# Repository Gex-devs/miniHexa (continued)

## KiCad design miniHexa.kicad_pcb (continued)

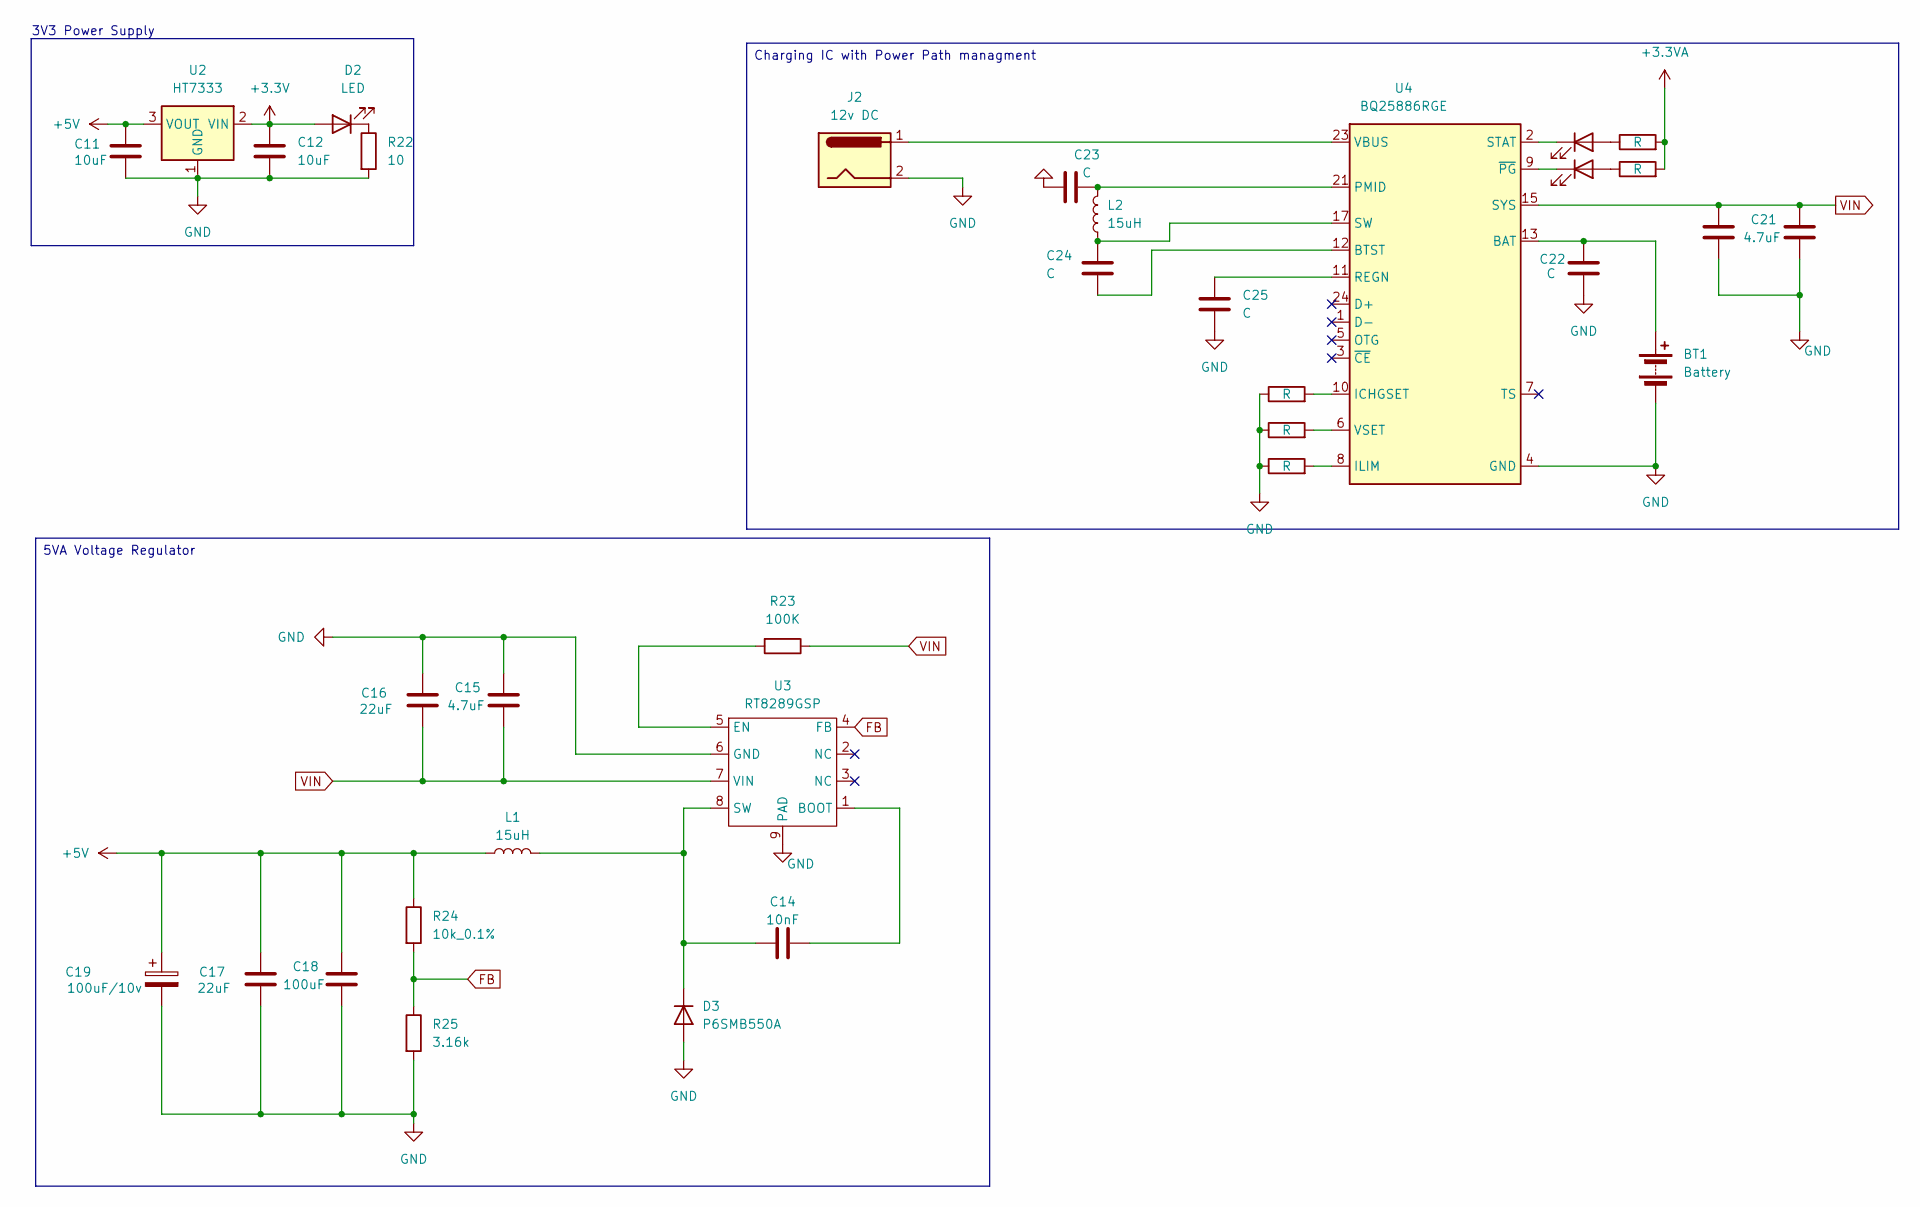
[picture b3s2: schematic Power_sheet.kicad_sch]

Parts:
BT1: Battery
C11, C12: 10uF; C_0805_2012Metric
C14: 10nF; C_0805_2012Metric
C15, C21: 4.7uF; C_0805_2012Metric
C16, C17, C20: 22uF; C_0805_2012Metric
C18: 100uF; C_0805_2012Metric
C19: 100uF/10v; C_0805_2012Metric
C22, C23, C24, C25: C; C_0805_2012Metric
D2, D4, D5: LED; LED_0805_2012Metric
D3: P6SMB550A; D_0805_2012Metric_Pad1.15x1.40mm_HandSolder
J2: 12v DC; BarrelJack_Wuerth_694102107102_1.0x3.9mm
L1, L2: 15uH; L_APV_APH0850
R22: 10; R_0805_2012Metric
R23: 100K; R_0805_2012Metric
R24: 10k_0.1%; R_0805_2012Metric
R25: 3.16k; R_0805_2012Metric
R26, R27, R28, R30, R31: R; R_0805_2012Metric
U2: HT7333; SOT-89-3
U3: RT8289GSP
U4: BQ25886RGE; Texas_RGE0024H_VQFN-24-1EP_4x4mm_P0.5mm_EP2.7x2.7mm

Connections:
+3.3V: C12.1, D2.2 (A), R27.2, R28.2, U2.2 (VIN); also elsewhere on the board
+5V: C11.1, C17.2, C18.2, C19.1, L1.1, R24.1, U2.3 (VOUT); also elsewhere on the board
FB: R24.2, R25.1, U3.4 (FB)
GND: BT1.2 (GND), C11.2, C12.2, C15.2, C16.2, C17.1, C18.1, C19.2, C20.1, C21.1, C22.2, C23.1, C25.2, D3.2 (A), J2.2, R22.2, R25.2, R26.1, R30.1, R31.1, U2.1 (GND), U3.6 (GND), U3.9 (PAD), U4.4 (GND), U4.19 (GND), U4.20 (GND), U4.25 (GND); also elsewhere on the board
unnamed: BT1.1 (+), C22.1, U4.13 (BAT), U4.14 (BAT)
unnamed: C23.2, L2.2, U4.21 (PMID), U4.22 (PMID)
unnamed: C24.1, L2.1, U4.17 (SW), U4.18 (SW)
unnamed: D2.1 (K), R22.1
unnamed: C14.1, D3.1 (K), L1.2, U3.8 (SW)
unnamed: D4.2 (A), R27.1
unnamed: D4.1 (K), U4.2 (STAT)
unnamed: D5.2 (A), R28.1
unnamed: D5.1 (K), U4.9 (~PG)
unnamed: C14.2, U3.1 (BOOT)
unnamed: R23.2, U3.5 (EN)
unnamed: C24.2, U4.12 (BTST)
unnamed: R26.2, U4.10 (ICHGSET)
unnamed: R31.2, U4.8 (ILIM)
unnamed: C25.1, U4.11 (REGN)
unnamed: J2.1, U4.23 (VBUS)
unnamed: R30.2, U4.6 (VSET)
VIN: C15.1, C16.1, C20.2, C21.2, R23.1, U3.7 (VIN), U4.15 (SYS), U4.16 (SYS)

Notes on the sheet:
3V3 Power Supply
Charging IC with Power Path managment
5VA Voltage Regulator

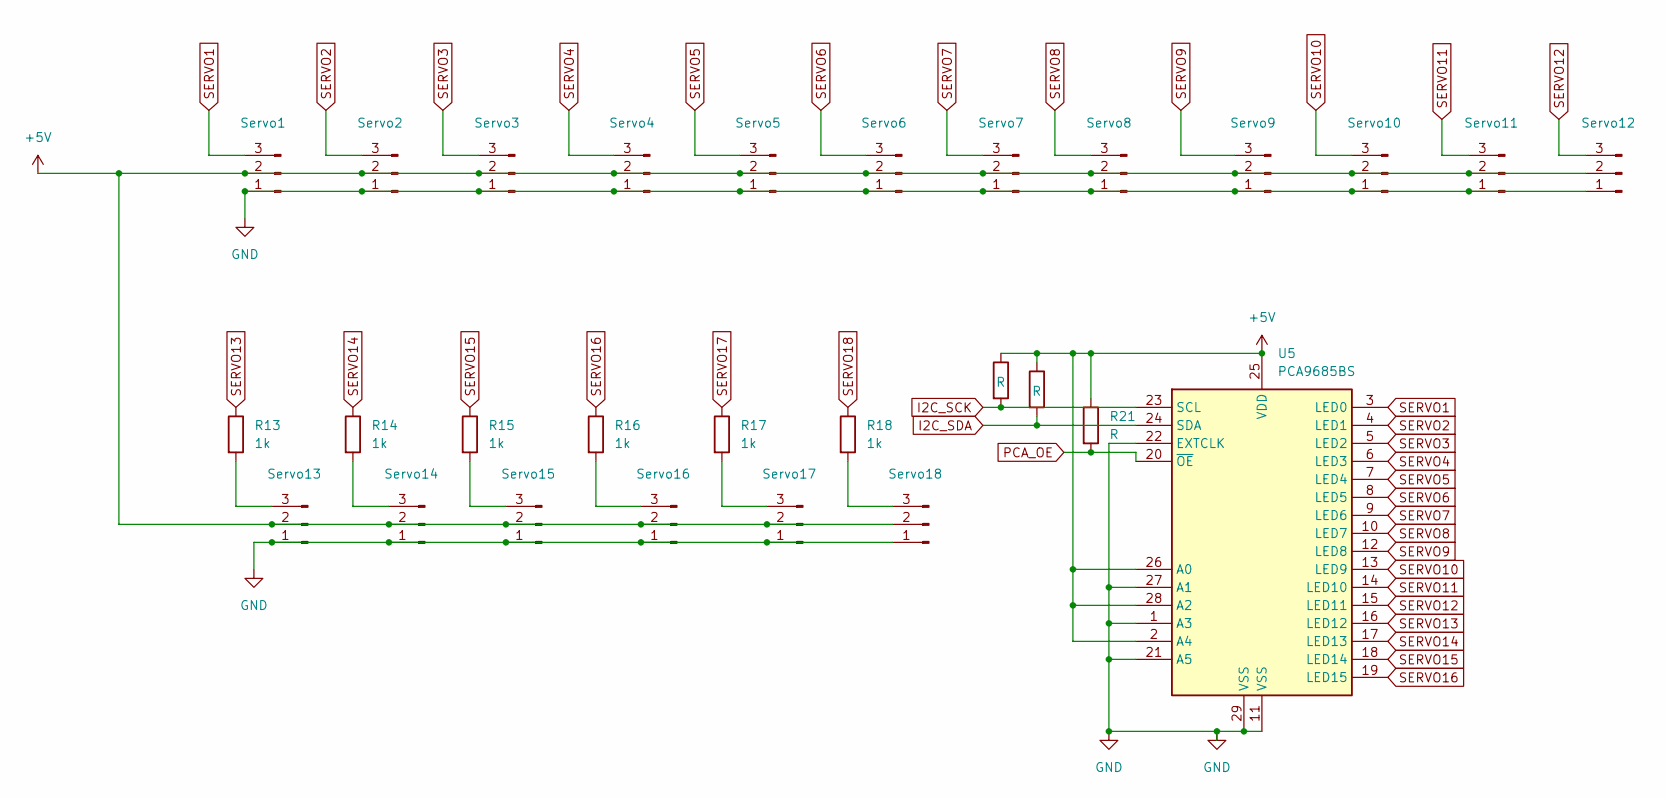
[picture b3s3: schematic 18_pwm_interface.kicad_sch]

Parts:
R13, R14, R15, R16, R17, R18: 1k; R_0805_2012Metric
R19, R20, R21: R; R_0805_2012Metric
Servo1, Servo2, Servo3, Servo4, Servo5, Servo6, Servo7, Servo8, Servo9, Servo10, Servo11, Servo12, Servo13, Servo14, Servo15, Servo16, Servo17, Servo18: Conn_01x03_Pin; JST_XH_B3B-XH-AM_1x03_P2.50mm_Vertical
U5: PCA9685BS; QFN-28-1EP_6x6mm_P0.65mm_EP4.25x4.25mm

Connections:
+5V: R19.1, R20.1, R21.1, Servo1.2, Servo2.2, Servo3.2, Servo4.2, Servo5.2, Servo6.2, Servo7.2, Servo8.2, Servo9.2, Servo10.2, Servo11.2, Servo12.2, Servo13.2, Servo14.2, Servo15.2, Servo16.2, Servo17.2, Servo18.2, U5.2 (A4), U5.25 (VDD), U5.26 (A0), U5.28 (A2); also elsewhere on the board
GND: Servo1.1, Servo2.1, Servo3.1, Servo4.1, Servo5.1, Servo6.1, Servo7.1, Servo8.1, Servo9.1, Servo10.1, Servo11.1, Servo12.1, Servo13.1, Servo14.1, Servo15.1, Servo16.1, Servo17.1, Servo18.1, U5.1 (A3), U5.11 (VSS), U5.21 (A5), U5.22 (EXTCLK), U5.27 (A1), U5.29 (VSS); also elsewhere on the board
I2C_SCK: R19.2, U5.23 (SCL); also elsewhere on the board
I2C_SDA: R20.2, U5.24 (SDA); also elsewhere on the board
unnamed: R13.2, Servo13.3
unnamed: R14.2, Servo14.3
unnamed: R15.2, Servo15.3
unnamed: R16.2, Servo16.3
unnamed: R17.2, Servo17.3
unnamed: R18.2, Servo18.3
PCA_OE: R21.2, U5.20 (~OE)
SERVO1: Servo1.3, U5.3 (LED0)
SERVO2: Servo2.3, U5.4 (LED1)
SERVO3: Servo3.3, U5.5 (LED2)
SERVO4: Servo4.3, U5.6 (LED3)
SERVO5: Servo5.3, U5.7 (LED4)
SERVO6: Servo6.3, U5.8 (LED5)
SERVO7: Servo7.3, U5.9 (LED6)
SERVO8: Servo8.3, U5.10 (LED7)
SERVO9: Servo9.3, U5.12 (LED8)
SERVO10: Servo10.3, U5.13 (LED9)
SERVO11: Servo11.3, U5.14 (LED10)
SERVO12: Servo12.3, U5.15 (LED11)
SERVO13: R13.1, U5.16 (LED12)
SERVO14: R14.1, U5.17 (LED13)
SERVO15: R15.1, U5.18 (LED14)
SERVO16: R16.1, U5.19 (LED15)
SERVO17: R17.1; also elsewhere on the board
SERVO18: R18.1; also elsewhere on the board

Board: 2 copper layers, 78 parts (2 on the bottom side), 58 nets, no tracks yet.

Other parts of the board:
MK-L1: INMP441-L; MIC_INMP441ACEZ-R7
MK-R1: INMP441-R; MIC_INMP441ACEZ-R7

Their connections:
+3.3V: MK-L1.7 (VDD), MK-R1.4 (L/R), MK-R1.7 (VDD); also elsewhere on the board
CHIPEN_MIC_L: MK-L1.8 (CHIPEN); also elsewhere on the board
CHIPEN_MIC_R: MK-R1.8 (CHIPEN); also elsewhere on the board
GND: MK-L1.4 (L/R), MK-L1.5 (GND), MK-L1.6 (GND), MK-L1.9 (GND), MK-R1.5 (GND), MK-R1.6 (GND), MK-R1.9 (GND); also elsewhere on the board
MIC_SCK: MK-L1.1 (SCK), MK-R1.1 (SCK); also elsewhere on the board
MIC_SD: MK-L1.3 (WS), MK-R1.3 (WS); also elsewhere on the board
MIC_WS: MK-L1.2 (SD), MK-R1.2 (SD); also elsewhere on the board

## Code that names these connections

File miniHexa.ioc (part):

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Mcu.Name=STM32F401R(D-E)Tx
Mcu.Package=LQFP64
Mcu.UserName=STM32F401RETx
PA11.GPIOParameters=GPIO_Label
PA11.GPIO_Label=USER_BUTTON
PA11.Signal=GPIO_Input
PA15.Mode=Half_Duplex_Master
PA15.Signal=I2S3_WS
PA2.GPIOParameters=GPIO_Label
PA2.GPIO_Label=UART2_LOG_TX
PA2.Mode=Asynchronous
PA2.Signal=USART2_TX
PA3.GPIOParameters=GPIO_Label
PA3.GPIO_Label=UART2_LOG_RX
PA3.Mode=Asynchronous
PA3.Signal=USART2_RX
PA5.Mode=Full_Duplex_Master
PA5.Signal=SPI1_SCK
PA6.Mode=Full_Duplex_Master
PA6.Signal=SPI1_MISO
PA7.Mode=Full_Duplex_Master
PA7.Signal=SPI1_MOSI
PA8.GPIOParameters=GPIO_Label
PA8.GPIO_Label=CHIP_EN
PA8.Signal=GPIO_Output
PB12.GPIOParameters=GPIO_Label
PB12.GPIO_Label=SPI_CS
PB12.Signal=GPIO_Output
PB6.GPIOParameters=GPIO_Label
PB6.GPIO_Label=SERVO_TX
PB6.Mode=Asynchronous
PB6.Signal=USART1_TX
PB7.GPIOParameters=GPIO_Label
PB7.GPIO_Label=SERVO_RX
PB7.Mode=Asynchronous
PB7.Signal=USART1_RX
PB8.Mode=I2C
PB8.Signal=I2C1_SCL
PB9.Mode=I2C
PB9.Signal=I2C1_SDA
PC10.Mode=Half_Duplex_Master
PC10.Signal=I2S3_CK
PC12.Mode=Half_Duplex_Master
PC12.Signal=I2S3_SD
PC6.Mode=Asynchronous
PC6.Signal=USART6_TX
PC7.Mode=Asynchronous
PC7.Signal=USART6_RX
PC8.GPIOParameters=GPIO_Label
PC8.GPIO_Label=SPI_RDY
PC8.Signal=GPIO_Output
PC9.GPIOParameters=GPIO_Label
PC9.GPIO_Label=IMU_INT
PC9.Signal=GPXTI9
PH0\ -\ OSC_IN.Mode=HSE-External-Clock-Source
PH0\ -\ OSC_IN.Signal=RCC_OSC_IN
PH1\ -\ OSC_OUT.Mode=HSE-External-Clock-Source
PH1\ -\ OSC_OUT.Signal=RCC_OSC_OUT
RCC.HSE_VALUE=25000000
RCC.SYSCLKFreq_VALUE=48000000
RCC.SYSCLKSource=RCC_SYSCLKSOURCE_PLLCLK
board=custom

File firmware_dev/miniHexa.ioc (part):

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Mcu.Name=STM32F401R(D-E)Tx
Mcu.Package=LQFP64
Mcu.UserName=STM32F401RETx
PA4.Mode=Half_Duplex_Master
PA4.Signal=I2S3_WS
PB0.Signal=S_TIM3_CH3
PB1.Signal=S_TIM3_CH4
PB6.Mode=I2C
PB6.Signal=I2C1_SCL
PB7.Mode=I2C
PB7.Signal=I2C1_SDA
PC10.Mode=Half_Duplex_Master
PC10.Signal=I2S3_CK
PC12.Mode=Half_Duplex_Master
PC12.Signal=I2S3_SD
RCC.HSE_VALUE=25000000
RCC.SYSCLKFreq_VALUE=16000000
board=custom

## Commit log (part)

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2025-10-26 Project Setup
2025-10-26 Moved folder and setup configuration
2025-10-26 Moved folder
2025-10-30 Updated schema
2026-03-15 update -- i don't remeber what
2026-03-24 moved firmware development to a different folder
2026-03-25 change mcu to STM32F401
2026-03-25 added stereo mics; cleaned up power management
2026-03-27 added Power IC managment with the DC input
2026-03-27 template wired the powerpath; removed useless interface
2026-03-30 added 16 channel servo PWM controller
2026-03-30 added PWM controller library
2026-03-31 assigned footprints and I2c for stm32
2026-04-01 Removed redundent components
2026-04-12 folder restructure
